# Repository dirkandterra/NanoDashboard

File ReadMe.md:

# _ESP_Dashboard_  

_This project uses the a Nano with a MCP2515 to drive a 2004 Dodge Intrepid Dashboard._

## How to use  

### Hardware Required  
* 2004 Dodge Intrepid Instrument Panel
* Connection:  

| Signal    | Intrepid  | Nano |
|-----------|-----------|------|
| 5V        | 5V		| 5V   |
| GLDATA    | GLDATA	| D4   |
| GLCLK     | GLCLK 	| D5   |
| LightLatch| LightLatch| D6   |
| Gauge CS  | Gauge CS  | D7   |
| VFDDATA   | VFDDATA   | D8   |
| VFDCLK	| VFDCLK	| D9   |
| VFD Pls	| VFD Pls	| D10  |
| Backlight | UC_LMP_DRV| D2   |
| PB Input  | ODO PB    | D3   |
| L Turn    | C2-5		| A0   |
| R Turn    | C1-8      | A1   |
| HighBeam  | C1-10     | A2   |
| OilPress  | C2-10     | A3   |
| ABS		| ??		| A4   |
| Airbag    | ??		| A5   |
| GND       | GND       | D7   |

* MCP2515 Breakout Board
* Connection: 

| MCP2515   | Nano |
|-----------|------|
| INT       |  -   |
| SCK		| D13  |
| MOSI      | D11  |
| MISO	    | D12  |
| CS to 5V  |  -   |
| GND       | GND  |
| 5V    	| 5V   |

### Arduino Library Needed  

```
https://github.com/coryjfowler/MCP_CAN_lib.git
```

* MCP_CAN_lib

### Intrepid Dashboard Help

* Intrepid Schematic (Not Complete):

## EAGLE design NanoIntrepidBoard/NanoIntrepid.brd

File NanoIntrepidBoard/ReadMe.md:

# _ESP_Dashboard_  

_This project uses the a Nano with a MCP2515 to drive a 2004 Dodge Intrepid Dashboard._

## How to use  

### Hardware Required  
* 2004 Dodge Intrepid Instrument Panel
* Connection:  

| Signal    | Intrepid  |ESP8266|
|-----------|-----------|-------|
| 3.3V      | NC		| VCC	|
| SCLK      | D0(SCL)   | GPIO14|
| VFDCLK	| VFDCLK	| Trans	| 
| MOSI      | VFD/GLDATA| GPIO13|
| Gauge CS  | Gauge CS  | GPIO16|
| Light Pls | Light Pls | GPIO12|
| VFD Pls	| VFD Pls	| GPIO02|
| GND       | GND       | GND   |

### Configure the project  

```
make menuconfig
```

* Set serial port under Serial Flasher Options.

### Build and Flash  

Build the project and flash it to the board, then run monitor tool to view serial output:

```
make -j4 flash monitor
```

(To exit the serial monitor, type ``Ctrl-]``.)

See the Getting Started Guide for full steps to configure and use ESP-IDF to build projects.

## Example Output  

* LOG:  

```
I (233) spi_oled: init gpio
I (235) gpio: GPIO[12]| InputEn: 0| OutputEn: 1| OpenDrain: 0| Pullup: 1| Pulldown: 0| Intr:0
I (239) gpio: GPIO[15]| InputEn: 0| OutputEn: 1| OpenDrain: 0| Pullup: 1| Pulldown: 0| Intr:0
I (251) spi_oled: init hspi
I (257) spi_oled: init oled
```

* Intrepid Schematic (Not Complete):

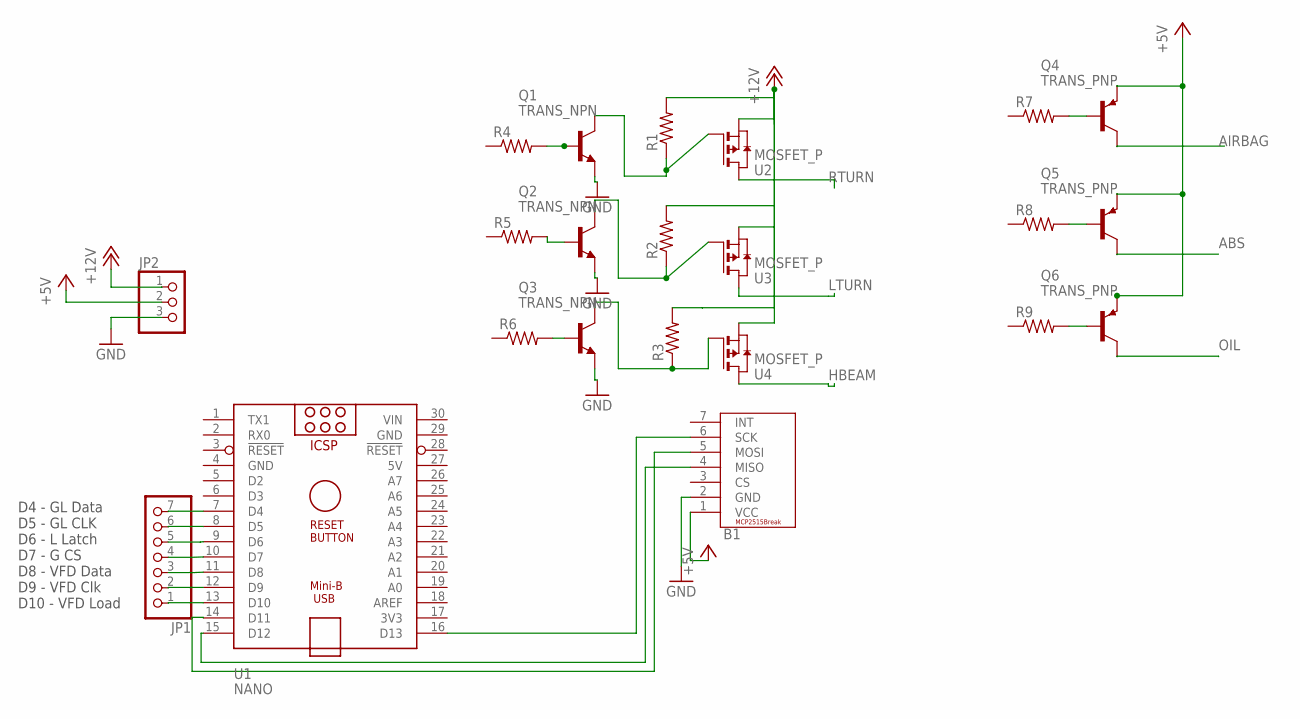
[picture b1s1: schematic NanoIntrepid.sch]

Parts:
B1: MCP2515_BREAKOUT
JP1: PINHD-1X7; 1X07
JP2: PINHD-1X3; 1X03
Q1, Q2, Q3: TRANS_NPN; SOT-23
Q4, Q5, Q6: TRANS_PNP; SOT-23
R1, R2, R3, R4, R5, R6, R7, R8, R9: R-US_M1206; M1206
U1: NANO
U2, U3, U4: MOSFET_P; SOT-23

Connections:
5V: U1.27 (5V)
+5V: B1.1 (VCC), JP2.2, Q4.3 (E), Q5.3 (E), Q6.3 (E)
+12V: JP2.1, R1.2, R2.2, R3.2, U2.2 (S), U3.2 (S), U4.2 (S)
ABS: Q5.2 (C)
ABS_UC: R8.1, U1.23 (A4)
AIRBAG: Q4.2 (C)
AIRBAG_UC: R7.1, U1.24 (A5)
GND: B1.2 (GND), JP2.3, Q1.2 (E), Q2.2 (E), Q3.2 (E), U1.4 (GND), U1.29 (GND)
HBEAM: U4.3 (D)
HB_UC: R4.1, U1.21 (A2)
LTURN: U3.3 (D)
LTURN_UC: R6.1, U1.19 (A0)
unnamed: B1.6 (SCK), U1.16 (D13)
unnamed: B1.4 (MISO), U1.15 (D12)
unnamed: B1.5 (MOSI), U1.14 (D11)
unnamed: JP1.7, U1.7 (D4)
unnamed: JP1.6, U1.8 (D5)
unnamed: JP1.5, U1.9 (D6)
unnamed: JP1.4, U1.10 (D7)
unnamed: JP1.3, U1.11 (D8)
unnamed: JP1.2, U1.12 (D9)
unnamed: JP1.1, U1.13 (D10)
unnamed: Q2.1 (B), R5.2
unnamed: Q1.1 (B), R4.2
unnamed: Q1.3 (C), R1.1, U2.1 (G)
unnamed: Q2.3 (C), R2.1, U3.1 (G)
unnamed: Q3.3 (C), R3.1, U4.1 (G)
unnamed: Q3.1 (B), R6.2
unnamed: Q4.1 (B), R7.2
unnamed: Q5.1 (B), R8.2
unnamed: Q6.1 (B), R9.2
OIL: Q6.2 (C)
OIL_UC: R9.1, U1.22 (A3)
PB: U1.6 (D3); also elsewhere on the board
RTURN: U2.3 (D)
RTURN_UC: R5.1, U1.20 (A1)
VIN: U1.30 (VIN)

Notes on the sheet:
D4 - GL Data D5 - GL CLK D6 - L Latch D7 - G CS D8 - VFD Data D9 - VFD Clk D10 - VFD Load

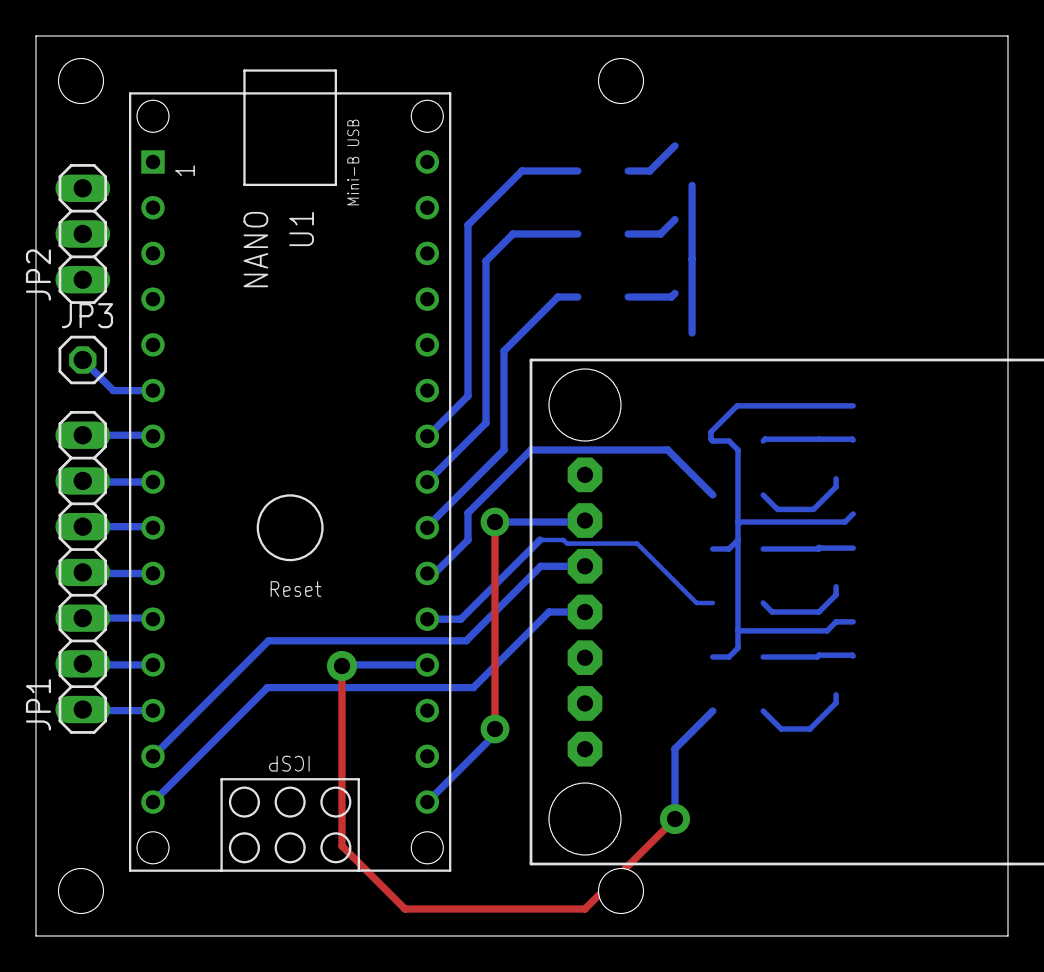
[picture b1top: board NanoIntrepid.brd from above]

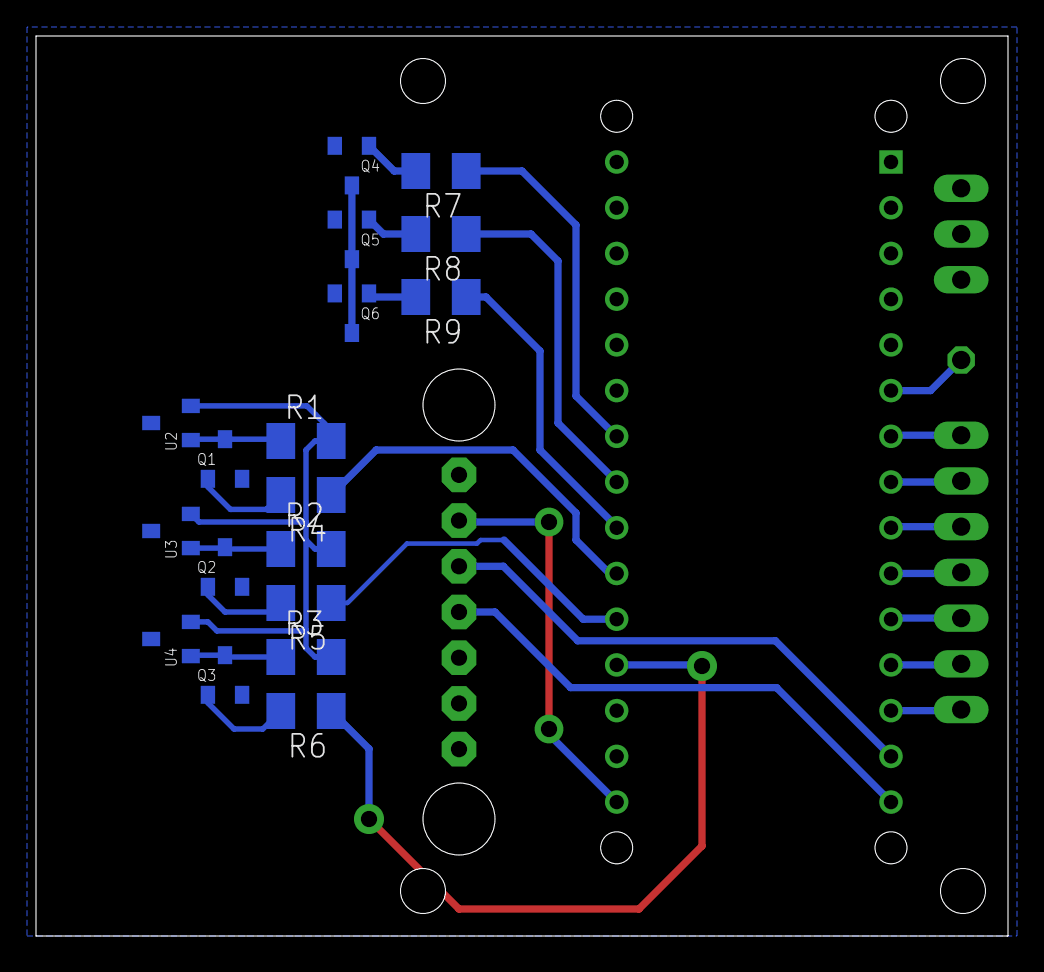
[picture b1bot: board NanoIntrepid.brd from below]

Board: 2 copper layers, 54.0 x 50.0 mm, 23 parts (18 on the bottom side), 29 nets.

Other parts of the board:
JP3: 1X01

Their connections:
PB: JP3.1; also elsewhere on the board

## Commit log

2024-09-19 Old Arduino Test Codes
2024-09-19 Add MCP2515 library
2024-10-13 Added some for troubleshooting gauge position
2024-10-14 Added Baseboard for Nano and MCP2515
2024-10-15 Fixed some Eagle Library mistakes and started laying out board
2024-10-16 Add Readme to project
2024-10-16 misplaced readme
2024-10-16 Added backlight pin to readme
2024-10-16 Worked on board files
2024-12-01 Finishing board file
2025-01-28 500 to get 250k
